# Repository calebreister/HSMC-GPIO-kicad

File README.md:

# HSMC-GPIO-kicad

This is a project created to test my new [HSMC Card KiCad footprints](https://github.com/KiCad/kicad-footprints/pulls?page=1&q=is%3Apr+is%3Aopen). It is based loosely on the [Terasis HSTC-GPIO Card](https://www.terasic.com.tw/cgi-bin/page/archive.pl?Language=English&No=322). In small quantities, the cost is comparable to the HSTC-GPIO Card.

## Features
- 40 GPIO pins
- Protection diodes and series resistors
- Power supply terminals
- Buffered I2C port with selectable voltage

## License
<br /><span xmlns:dct="http://purl.org/dc/terms/" property="dct:title">HSMC-GPIO-kicad</span> by <a xmlns:cc="http://creativecommons.org/ns#" href="https://github.com/calebreister/" property="cc:attributionName" rel="cc:attributionURL">Caleb Reister</a> is licensed under a <a rel="license" href="http://creativecommons.org/licenses/by-sa/4.0/">Creative Commons Attribution-ShareAlike 4.0 International License</a>.

## Pictures

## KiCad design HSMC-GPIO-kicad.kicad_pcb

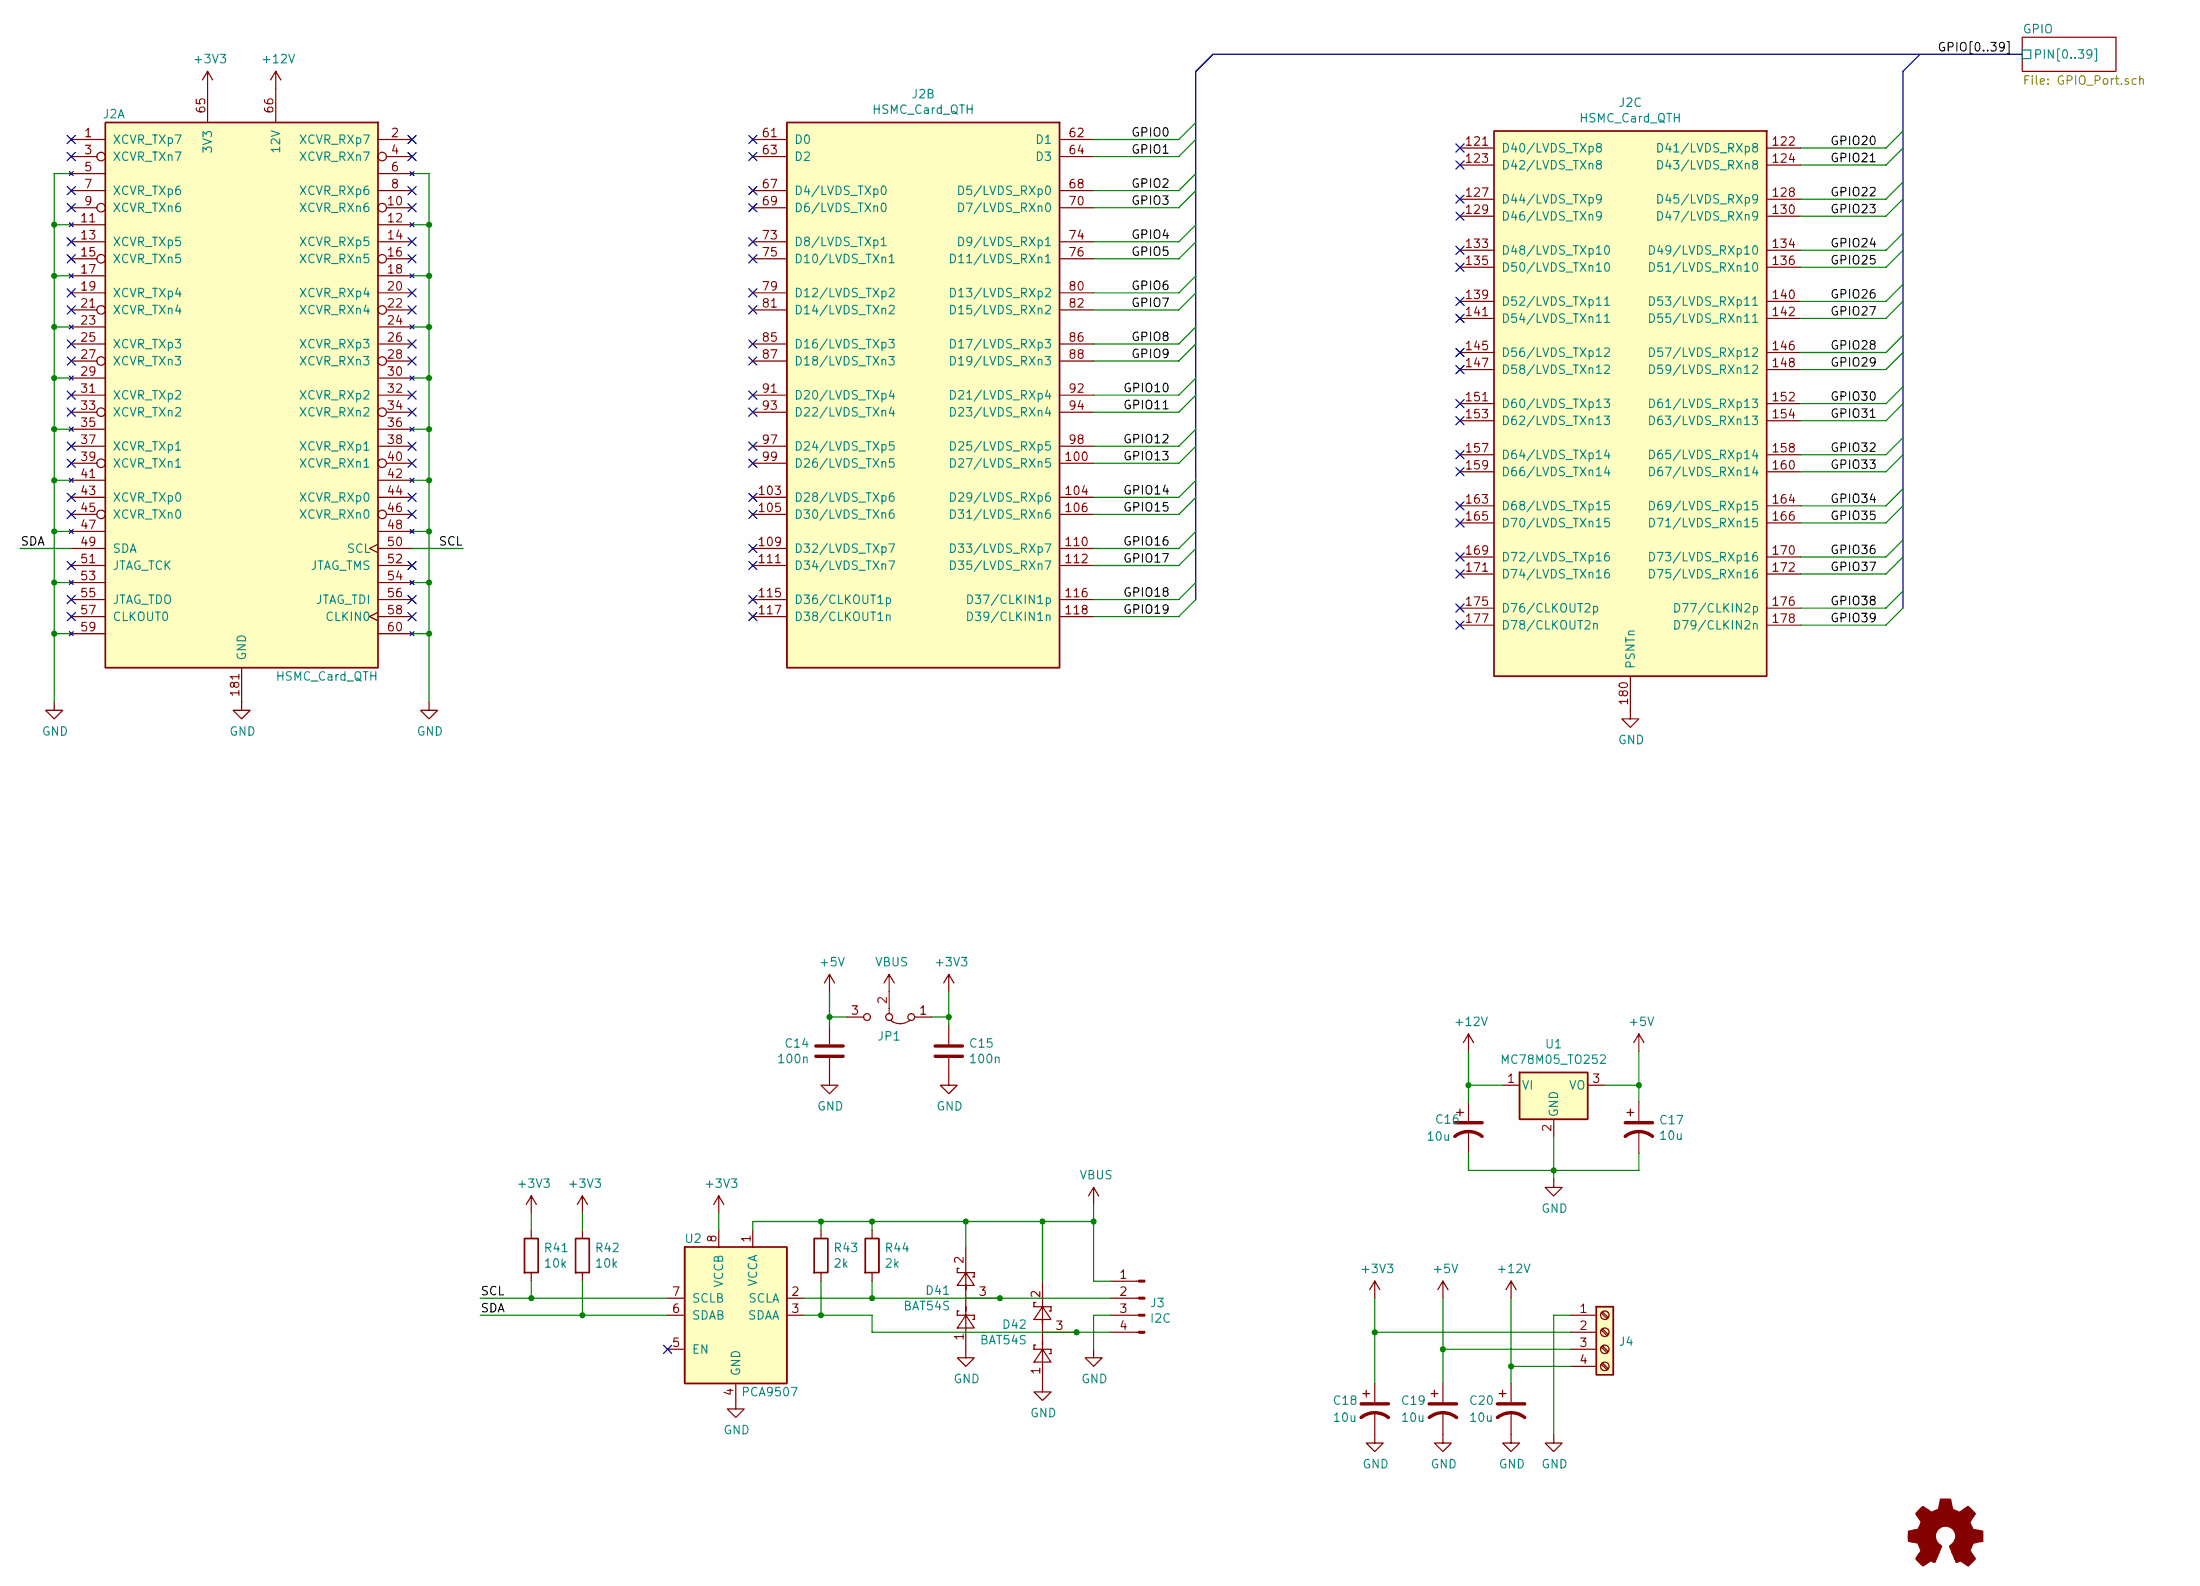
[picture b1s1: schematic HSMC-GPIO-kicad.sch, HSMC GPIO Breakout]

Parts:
C14, C15: 100n; C_0805_2012Metric
C16, C17, C18, C19, C20: 10u; CP_EIA-3528-21_Kemet-B
D41, D42: BAT54S; SOT-23
J2: HSMC_Card_QTH; Samtec_HSMC_Card_QTH-090-01-x-D-A_3.076x0.932in_P0.5mm_Vert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
J3: I2C; PinHeader_1x04_P2.54mm_Vertical
J4: Screw_Terminal_01x04; TerminalBlock_bornier-4_P5.08mm
JP1: Jumper_3_Bridged12; PinHeader_1x03_P2.54mm_Vertical
LOGO1: Logo_Open_Hardware_Small; OSHW-Symbol_6.7x6mm_SilkScreen
R41, R42: 10k; R_0603_1608Metric
R43, R44: 2k; R_0603_1608Metric
U1: MC78M05_TO252; TO-252-2
U2: PCA9507; SOIC-8_3.9x4.9mm_P1.27mm

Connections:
+3V3: C15.2, C18.1, J2.65 (3V3), J2.71 (3V3), J2.77 (3V3), J2.83 (3V3), J2.89 (3V3), J2.95 (3V3), J2.101 (3V3), J2.107 (3V3), J2.113 (3V3), J2.119 (3V3), J2.125 (3V3), J2.131 (3V3), J2.137 (3V3), J2.143 (3V3), J2.149 (3V3), J2.155 (3V3), J2.161 (3V3), J2.167 (3V3), J2.173 (3V3), J2.179 (3V3), J4.2, JP1.1 (A), R41.1, R42.1, U2.8 (VCCB); also elsewhere on the board
+5V: C14.2, C17.1, C19.1, J4.3, JP1.3 (B), U1.3 (VO)
+12V: C16.1, C20.1, J2.66 (12V), J2.72 (12V), J2.78 (12V), J2.84 (12V), J2.90 (12V), J2.96 (12V), J2.102 (12V), J2.108 (12V), J2.114 (12V), J2.120 (12V), J2.126 (12V), J2.132 (12V), J2.138 (12V), J2.144 (12V), J2.150 (12V), J2.156 (12V), J2.162 (12V), J2.168 (12V), J2.174 (12V), J4.4, U1.1 (VI)
/GPIO0: J2.62 (D1); also elsewhere on the board
/GPIO1: J2.64 (D3); also elsewhere on the board
/GPIO2: J2.68 (D5/LVDS_RXp0); also elsewhere on the board
/GPIO3: J2.70 (D7/LVDS_RXn0); also elsewhere on the board
/GPIO4: J2.74 (D9/LVDS_RXp1); also elsewhere on the board
/GPIO5: J2.76 (D11/LVDS_RXn1); also elsewhere on the board
/GPIO6: J2.80 (D13/LVDS_RXp2); also elsewhere on the board
/GPIO7: J2.82 (D15/LVDS_RXn2); also elsewhere on the board
/GPIO8: J2.86 (D17/LVDS_RXp3); also elsewhere on the board
/GPIO9: J2.88 (D19/LVDS_RXn3); also elsewhere on the board
/GPIO10: J2.92 (D21/LVDS_RXp4); also elsewhere on the board
/GPIO11: J2.94 (D23/LVDS_RXn4); also elsewhere on the board
/GPIO12: J2.98 (D25/LVDS_RXp5); also elsewhere on the board
/GPIO13: J2.100 (D27/LVDS_RXn5); also elsewhere on the board
/GPIO14: J2.104 (D29/LVDS_RXp6); also elsewhere on the board
/GPIO15: J2.106 (D31/LVDS_RXn6); also elsewhere on the board
/GPIO16: J2.110 (D33/LVDS_RXp7); also elsewhere on the board
/GPIO17: J2.112 (D35/LVDS_RXn7); also elsewhere on the board
/GPIO18: J2.116 (D37/CLKIN1p); also elsewhere on the board
/GPIO19: J2.118 (D39/CLKIN1n); also elsewhere on the board
/GPIO20: J2.122 (D41/LVDS_RXp8); also elsewhere on the board
/GPIO21: J2.124 (D43/LVDS_RXn8); also elsewhere on the board
/GPIO22: J2.128 (D45/LVDS_RXp9); also elsewhere on the board
/GPIO23: J2.130 (D47/LVDS_RXn9); also elsewhere on the board
/GPIO24: J2.134 (D49/LVDS_RXp10); also elsewhere on the board
/GPIO25: J2.136 (D51/LVDS_RXn10); also elsewhere on the board
/GPIO26: J2.140 (D53/LVDS_RXp11); also elsewhere on the board
/GPIO27: J2.142 (D55/LVDS_RXn11); also elsewhere on the board
/GPIO28: J2.146 (D57/LVDS_RXp12); also elsewhere on the board
/GPIO29: J2.148 (D59/LVDS_RXn12); also elsewhere on the board
/GPIO30: J2.152 (D61/LVDS_RXp13); also elsewhere on the board
/GPIO31: J2.154 (D63/LVDS_RXn13); also elsewhere on the board
/GPIO32: J2.158 (D65/LVDS_RXp14); also elsewhere on the board
/GPIO33: J2.160 (D67/LVDS_RXn14); also elsewhere on the board
/GPIO34: J2.164 (D69/LVDS_RXp15); also elsewhere on the board
/GPIO35: J2.166 (D71/LVDS_RXn15); also elsewhere on the board
/GPIO36: J2.170 (D73/LVDS_RXp16); also elsewhere on the board
/GPIO37: J2.172 (D75/LVDS_RXn16); also elsewhere on the board
/GPIO38: J2.176 (D77/CLKIN2p); also elsewhere on the board
/GPIO39: J2.178 (D79/CLKIN2n); also elsewhere on the board
/SCL: J2.50 (SCL), R41.2, U2.7 (SCLB)
/SDA: J2.49 (SDA), R42.2, U2.6 (SDAB)
GND: C14.1, C15.1, C16.2, C17.2, C18.2, C19.2, C20.2, D41.1, D42.1, J2.5, J2.6, J2.11, J2.12, J2.17, J2.18, J2.23, J2.24, J2.29, J2.30, J2.35, J2.36, J2.41, J2.42, J2.47, J2.48, J2.53, J2.54, J2.59, J2.60, J2.180 (PSNTn), J2.181 (GND), J2.182 (GND), J2.183 (GND), J2.184 (GND), J2.185 (GND), J2.186 (GND), J2.187 (GND), J2.188 (GND), J2.189 (GND), J2.190 (GND), J2.191 (GND), J2.192 (GND), J3.3, J4.1, U1.2 (GND), U2.4 (GND); also elsewhere on the board
unnamed: D41.3, J3.2, R44.2, U2.2 (SCLA)
unnamed: D42.3, J3.4, R43.2, U2.3 (SDAA)
VBUS: D41.2, D42.2, J3.1, JP1.2 (C), R43.1, R44.1, U2.1 (VCCA)

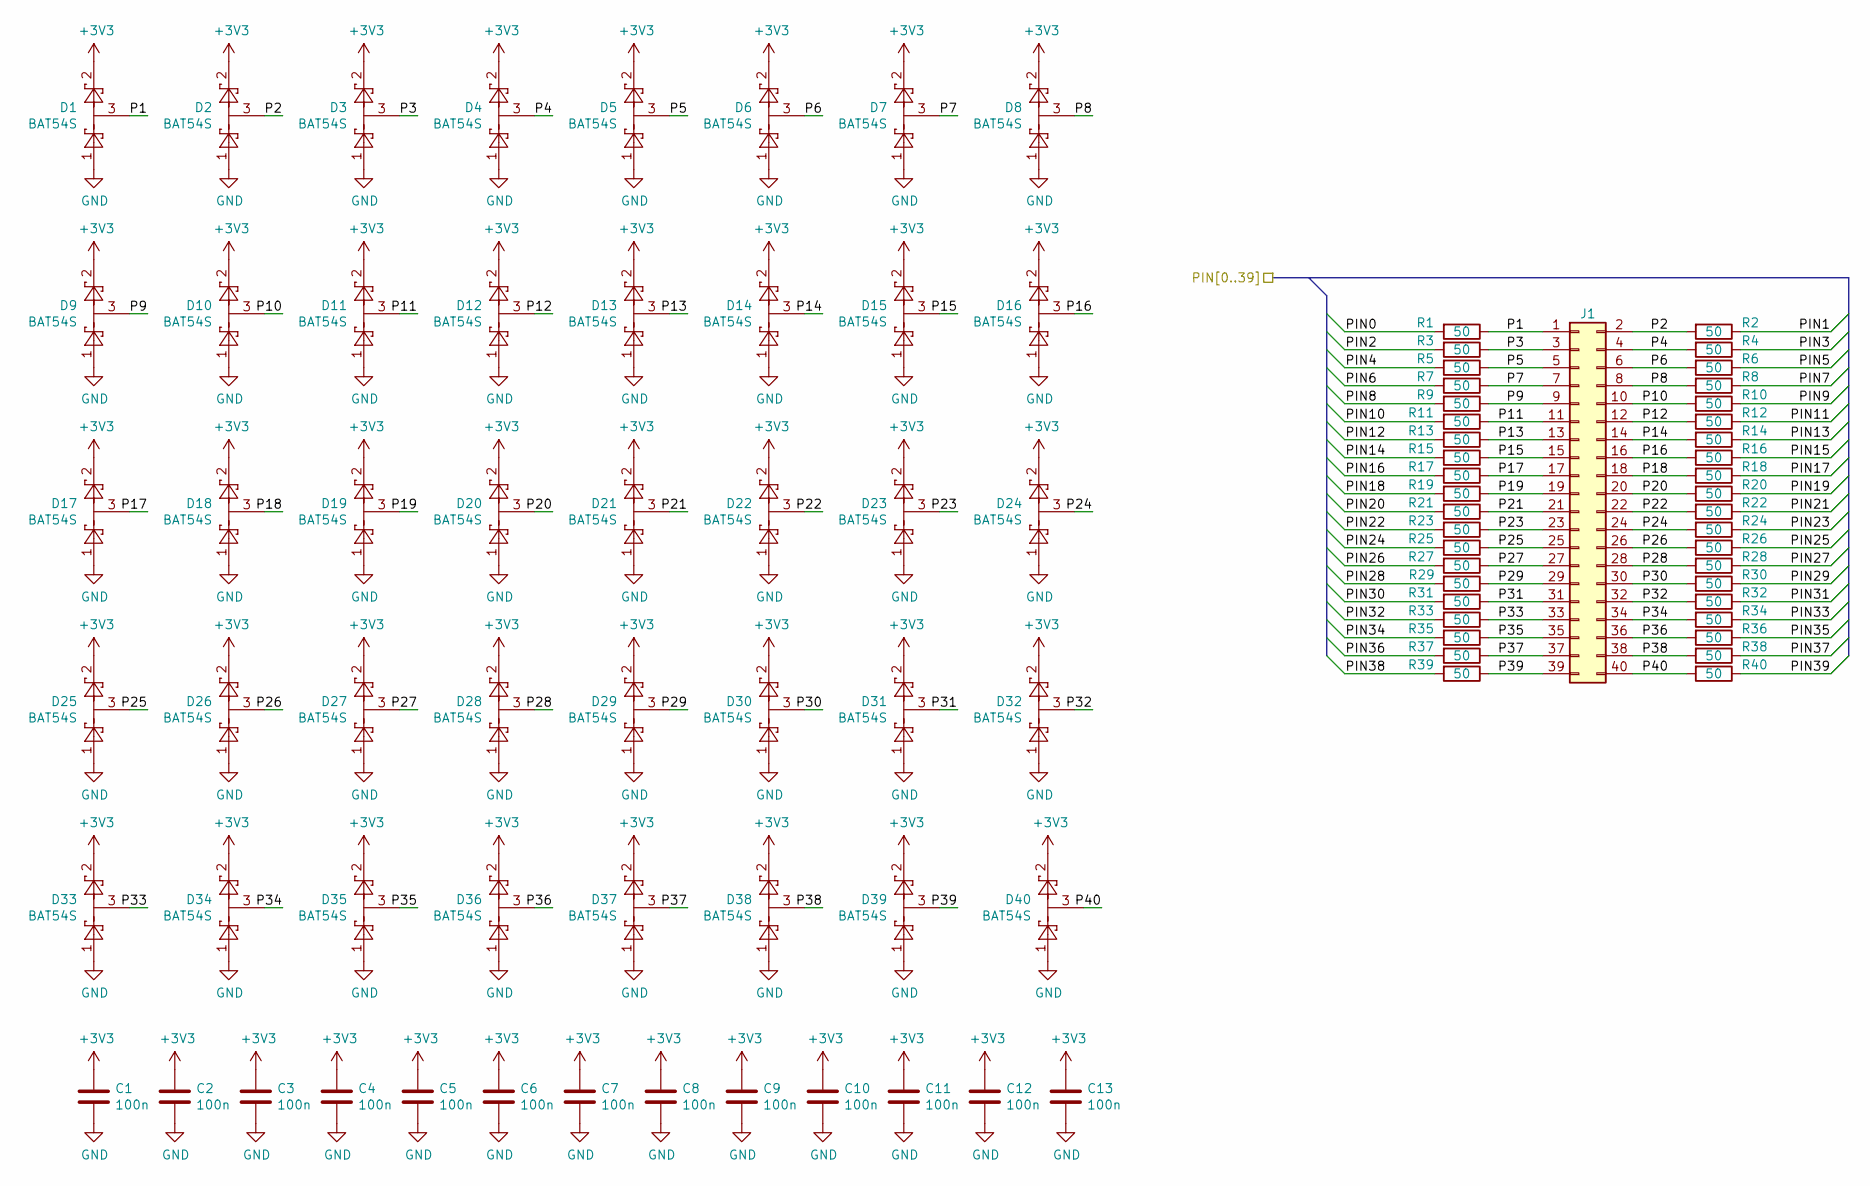
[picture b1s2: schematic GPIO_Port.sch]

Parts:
C1, C2, C3, C4, C5, C6, C7, C8, C9, C10, C11, C12, C13: 100n; C_0805_2012Metric
D1, D2, D3, D4, D5, D6, D7, D8, D9, D10, D11, D12, D13, D14, D15, D16, D17, D18, D19, D20, D21, D22, D23, D24, D25, D26, D27, D28, D29, D30, D31, D32, D33, D34, D35, D36, D37, D38, D39, D40: BAT54S; SOT-323_SC-70
J1: Conn_02x20_Odd_Even; IDC-Header_2x20_P2.54mm_Vertical
R1, R2, R3, R4, R5, R6, R7, R8, R9, R10, R11, R12, R13, R14, R15, R16, R17, R18, R19, R20, R21, R22, R23, R24, R25, R26, R27, R28, R29, R30, R31, R32, R33, R34, R35, R36, R37, R38, R39, R40: 50; R_0603_1608Metric

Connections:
+3V3: C1.1, C2.1, C3.1, C4.1, C5.1, C6.1, C7.1, C8.1, C9.1, C10.1, C11.1, C12.1, C13.1, D1.2, D2.2, D3.2, D4.2, D5.2, D6.2, D7.2, D8.2, D9.2, D10.2, D11.2, D12.2, D13.2, D14.2, D15.2, D16.2, D17.2, D18.2, D19.2, D20.2, D21.2, D22.2, D23.2, D24.2, D25.2, D26.2, D27.2, D28.2, D29.2, D30.2, D31.2, D32.2, D33.2, D34.2, D35.2, D36.2, D37.2, D38.2, D39.2, D40.2; also elsewhere on the board
/GPIO0: R1.2; also elsewhere on the board
/GPIO1: R2.1; also elsewhere on the board
/GPIO2: R3.2; also elsewhere on the board
/GPIO3: R4.1; also elsewhere on the board
/GPIO4: R5.2; also elsewhere on the board
/GPIO5: R6.1; also elsewhere on the board
/GPIO6: R7.2; also elsewhere on the board
/GPIO7: R8.1; also elsewhere on the board
/GPIO8: R9.2; also elsewhere on the board
/GPIO9: R10.1; also elsewhere on the board
/GPIO10: R11.2; also elsewhere on the board
/GPIO11: R12.1; also elsewhere on the board
/GPIO12: R13.2; also elsewhere on the board
/GPIO13: R14.1; also elsewhere on the board
/GPIO14: R15.2; also elsewhere on the board
/GPIO15: R16.1; also elsewhere on the board
/GPIO16: R17.2; also elsewhere on the board
/GPIO17: R18.1; also elsewhere on the board
/GPIO18: R19.2; also elsewhere on the board
/GPIO19: R20.1; also elsewhere on the board
/GPIO20: R21.2; also elsewhere on the board
/GPIO21: R22.1; also elsewhere on the board
/GPIO22: R23.2; also elsewhere on the board
/GPIO23: R24.1; also elsewhere on the board
/GPIO24: R25.2; also elsewhere on the board
/GPIO25: R26.1; also elsewhere on the board
/GPIO26: R27.2; also elsewhere on the board
/GPIO27: R28.1; also elsewhere on the board
/GPIO28: R29.2; also elsewhere on the board
/GPIO29: R30.1; also elsewhere on the board
/GPIO30: R31.2; also elsewhere on the board
/GPIO31: R32.1; also elsewhere on the board
/GPIO32: R33.2; also elsewhere on the board
/GPIO33: R34.1; also elsewhere on the board
/GPIO34: R35.2; also elsewhere on the board
/GPIO35: R36.1; also elsewhere on the board
/GPIO36: R37.2; also elsewhere on the board
/GPIO37: R38.1; also elsewhere on the board
/GPIO38: R39.2; also elsewhere on the board
/GPIO39: R40.1; also elsewhere on the board
/GPIO/P1: D1.3, J1.1, R1.1
/GPIO/P2: D2.3, J1.2, R2.2
/GPIO/P3: D3.3, J1.3, R3.1
/GPIO/P4: D4.3, J1.4, R4.2
/GPIO/P5: D5.3, J1.5, R5.1
/GPIO/P6: D6.3, J1.6, R6.2
/GPIO/P7: D7.3, J1.7, R7.1
/GPIO/P8: D8.3, J1.8, R8.2
/GPIO/P9: D9.3, J1.9, R9.1
/GPIO/P10: D10.3, J1.10, R10.2
/GPIO/P11: D11.3, J1.11, R11.1
/GPIO/P12: D12.3, J1.12, R12.2
/GPIO/P13: D13.3, J1.13, R13.1
/GPIO/P14: D14.3, J1.14, R14.2
/GPIO/P15: D15.3, J1.15, R15.1
/GPIO/P16: D16.3, J1.16, R16.2
/GPIO/P17: D17.3, J1.17, R17.1
/GPIO/P18: D18.3, J1.18, R18.2
/GPIO/P19: D19.3, J1.19, R19.1
/GPIO/P20: D20.3, J1.20, R20.2
/GPIO/P21: D21.3, J1.21, R21.1
/GPIO/P22: D22.3, J1.22, R22.2
/GPIO/P23: D23.3, J1.23, R23.1
/GPIO/P24: D24.3, J1.24, R24.2
/GPIO/P25: D25.3, J1.25, R25.1
/GPIO/P26: D26.3, J1.26, R26.2
/GPIO/P27: D27.3, J1.27, R27.1
/GPIO/P28: D28.3, J1.28, R28.2
/GPIO/P29: D29.3, J1.29, R29.1
/GPIO/P30: D30.3, J1.30, R30.2
/GPIO/P31: D31.3, J1.31, R31.1
/GPIO/P32: D32.3, J1.32, R32.2
/GPIO/P33: D33.3, J1.33, R33.1
/GPIO/P34: D34.3, J1.34, R34.2
/GPIO/P35: D35.3, J1.35, R35.1
/GPIO/P36: D36.3, J1.36, R36.2
/GPIO/P37: D37.3, J1.37, R37.1
/GPIO/P38: D38.3, J1.38, R38.2
/GPIO/P39: D39.3, J1.39, R39.1
/GPIO/P40: D40.3, J1.40, R40.2
GND: C1.2, C2.2, C3.2, C4.2, C5.2, C6.2, C7.2, C8.2, C9.2, C10.2, C11.2, C12.2, C13.2, D1.1, D2.1, D3.1, D4.1, D5.1, D6.1, D7.1, D8.1, D9.1, D10.1, D11.1, D12.1, D13.1, D14.1, D15.1, D16.1, D17.1, D18.1, D19.1, D20.1, D21.1, D22.1, D23.1, D24.1, D25.1, D26.1, D27.1, D28.1, D29.1, D30.1, D31.1, D32.1, D33.1, D34.1, D35.1, D36.1, D37.1, D38.1, D39.1, D40.1; also elsewhere on the board

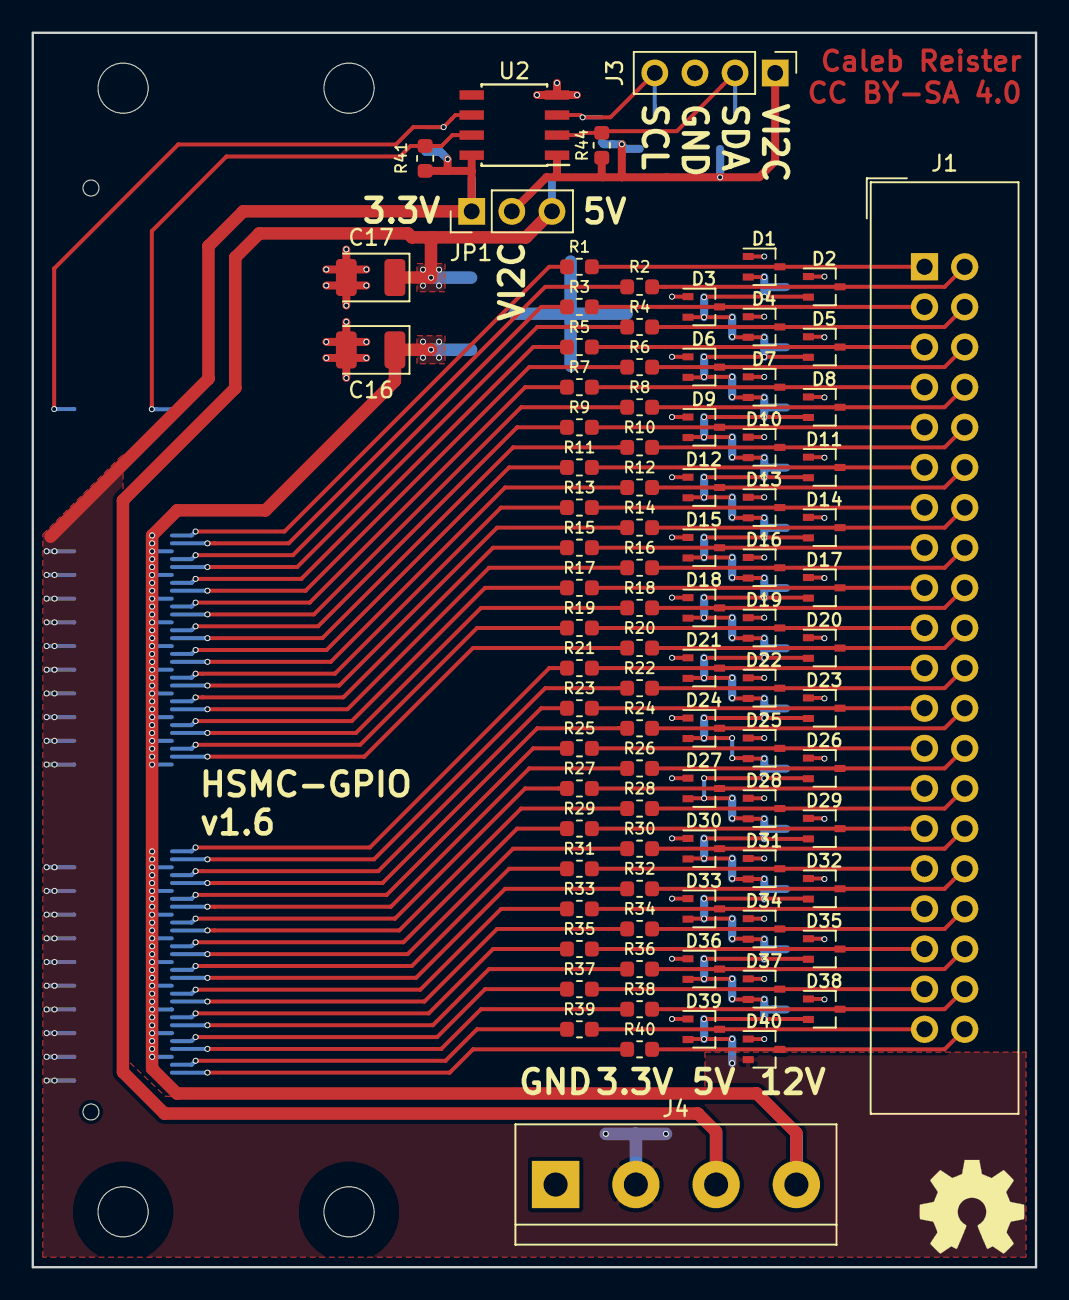
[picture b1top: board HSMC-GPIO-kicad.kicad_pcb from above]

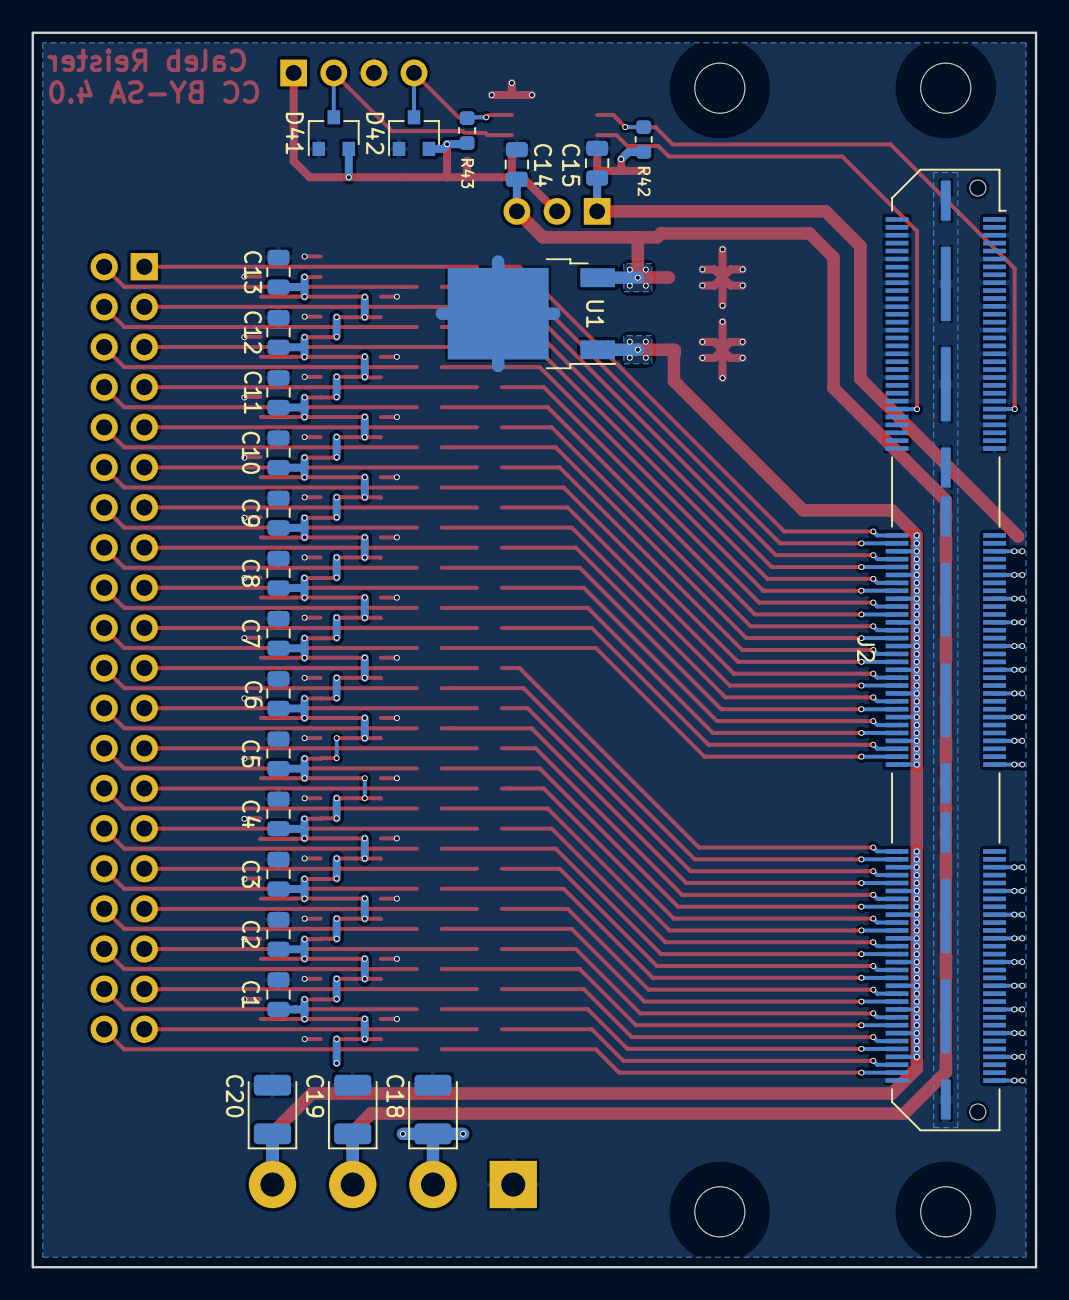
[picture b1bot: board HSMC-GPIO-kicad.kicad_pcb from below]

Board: 2 copper layers, 63.5 x 78.1 mm, 114 parts (24 on the bottom side), 89 nets.

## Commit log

2018-09-12 Finish initial schematic, work on PCB design
2018-09-12 Reroute ribbon connector protection circuitry, switch to single ribbon cable configuration.
2018-09-13 Change pin/bus labels in schematic
2018-09-14 Begin routing ribbon cable connector
2018-09-14 Continue routing GPIO ribbon connector
2018-09-15 Finish routing GPIO port
2018-09-15 Adjust board and plane sizes
2018-09-20 Finish initial placement and routing
2018-09-20 Fix major error in HSMC footprints
2018-09-20 Reroute GPIO pins (again)
2018-09-20 Change BAT54S diode packages back to to SOT-23
2018-09-21 Fix issues and reroute I2C buffer, length match GPIO bus
2018-09-22 Rotate GPIO connector 180deg, reroute
2018-09-22 Clean-up, generate Gerber & drill files
2018-10-02 Modify and submit to Sunstone for DFM report.
2018-10-02 Re-place protection diodes/resistors, change diode packages to SOT-323
2018-10-08 Reroute GPIO, 5V regulator, and I2C buffer
2018-10-15 Minor footprint and position adjustments
2018-10-22 Modify board to meet OSH Park specs, remove old HSMC card library.
2018-11-13 Modify power terminal
2018-11-13 Change to 5.08mm power terminal, other minor modifications.
2019-01-16 Updated to use new KLC-compliant symbols and footprints
2019-01-16 Add license notice to README.md
2019-01-16 Add license to PCB and increment version number
2019-01-16 Add project images
2019-01-16 Update fabrication outputs to v1.6.

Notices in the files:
HSMC-GPIO-kicad.kicad_pcb:
CC BY-SA 4.0
